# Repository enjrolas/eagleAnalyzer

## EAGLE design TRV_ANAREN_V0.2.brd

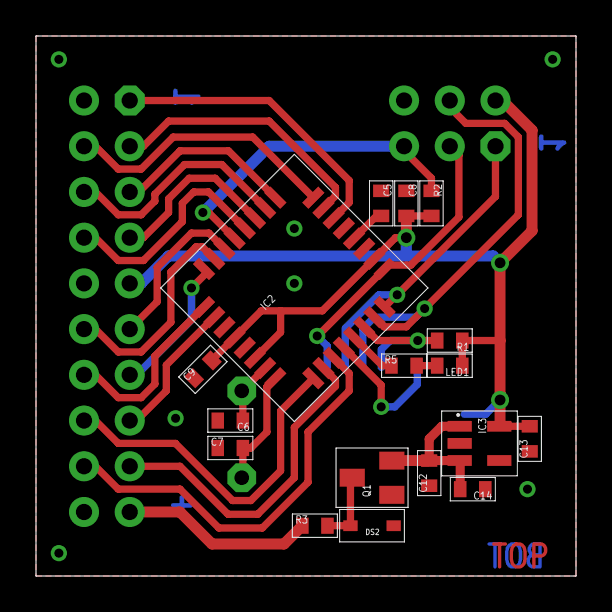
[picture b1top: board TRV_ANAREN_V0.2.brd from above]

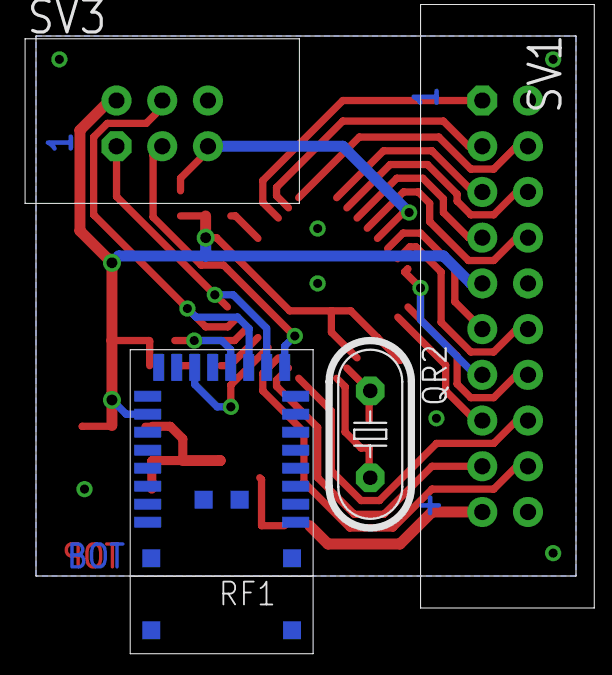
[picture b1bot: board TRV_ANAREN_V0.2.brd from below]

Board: 2 copper layers, 30.0 x 30.0 mm, 21 parts (4 on the bottom side), 31 nets.

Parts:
C5, C8, C9, C14: 100n; 0603
C6, C7: 22p; 0603
C12, C13: 1u; 0603
DS2: PESD12VL1BA; SOD323
IC2: MEGA168PA-AU; TQFP32-08
IC3: LP2992-IM5-3.3; SOT23-5
LED1: LEDR; 0603
Q1: IRLM9301; SOT23
QR2: 16.000; HC49U-V
R1, R2: 10k; 0603
R3: 0R; 0603
R5: 330R; 0603
RF1: ANAREN
SV1: ISP; ML20
SV3: ISP; ML6

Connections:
+3V3: C8.2, C9.2, C13.2, IC2.4, IC2.6, IC2.18, IC3.5, LED1.1, R1.1, R2.2, RF1.18, SV1.9, SV3.2
GND: C5.1, C6.2, C7.1, C8.1, C9.1, C12.1, C13.1, C14.1, DS2.C, IC2.3, IC2.5, IC2.21, IC3.2, Q1.1, RF1.8, RF1.17, SV1.10, SV1.20, SV3.6
LED: IC2.13, R5.1
MISO: IC2.16, RF1.10, SV3.1
MOSI: IC2.15, RF1.11, SV3.4
unnamed: IC2.22, SV1.1
unnamed: DS2.A, Q1.3, R3.2
unnamed: C5.2, IC2.20
unnamed: C12.2, C14.2, IC3.1, IC3.3, Q1.2
unnamed: C6.1, IC2.7, QR2.1
unnamed: C7.2, IC2.8, QR2.2
unnamed: LED1.2, R5.2
unnamed: R3.1, SV1.19
PC0: IC2.23, SV1.3
PC1: IC2.24, SV1.4
PC2: IC2.25, SV1.5
PC3: IC2.26, SV1.6
PC4: IC2.27, SV1.7
PC5: IC2.28, SV1.8
PD2: IC2.32, SV1.13
PD3: IC2.1, SV1.14
PD4: IC2.2, SV1.15
PD5: IC2.9, SV1.16
PD6: IC2.10, SV1.17
PD7: IC2.11, SV1.18
RIRQ: IC2.12, RF1.14
RSEL: IC2.14, R1.2, RF1.12
RST: IC2.29, R2.1, SV3.5
RXD: IC2.30, SV1.11
SCK: IC2.17, RF1.9, SV3.3
TXD: IC2.31, SV1.12

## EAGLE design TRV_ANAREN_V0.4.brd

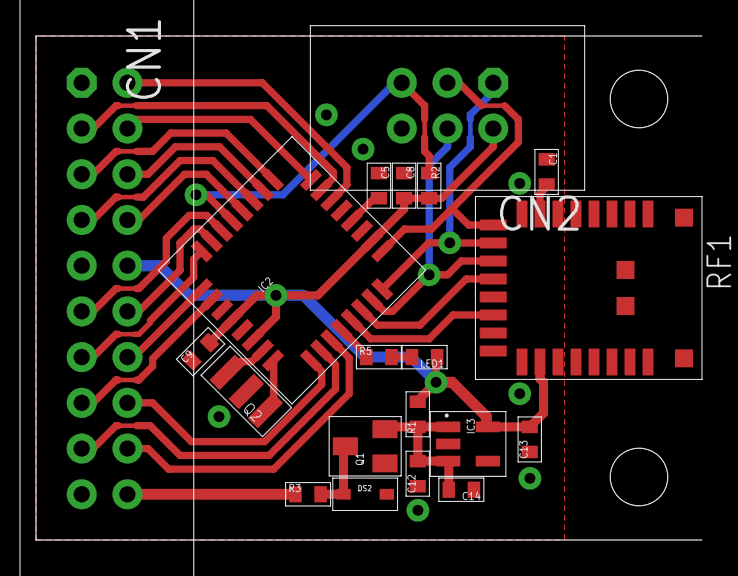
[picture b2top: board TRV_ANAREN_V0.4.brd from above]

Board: 2 copper layers, 37.0 x 28.0 mm, 20 parts (0 on the bottom side), 32 nets.

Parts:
C1: n.b.; 0603
C5, C8, C9, C14: 100n; 0603
C12, C13: 1u; 0603
CN1: EXT; ML20
CN2: ISP; ML6
DS2: PESD12VL1BA; SOD323
IC2: MEGA168PA-AU; TQFP32-08
IC3: LP2992-IM5-3.3; SOT23-5
LED1: LEDR; 0603
Q1: IRLM9301; SOT23
Q2: CR
R1: n.b.; 0603
R2: 10k; 0603
R3: 0R; 0603
R5: 330R; 0603
RF1: ANAREN_C

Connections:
+3V3: C8.2, C9.2, C13.2, CN1.10, CN2.2, IC2.4, IC2.6, IC2.18, IC3.5, LED1.1, R1.2, R2.2, RF1.18
GND: C1.1, C5.1, C8.1, C9.1, C12.1, C13.1, C14.1, CN1.9, CN1.19, CN2.6, DS2.A, IC2.3, IC2.5, IC2.21, IC3.2, Q1.1, Q2.M, RF1.8, RF1.17
MISO: CN2.1, IC2.16, RF1.10
MOSI: CN2.4, IC2.15, RF1.11
unnamed: C1.2, RF1.7
unnamed: IC2.12, R5.1
unnamed: CN1.2, IC2.22
unnamed: DS2.C, Q1.3, R3.2
unnamed: C5.2, IC2.20
unnamed: C12.2, C14.2, IC3.1, IC3.3, Q1.2, R1.1
unnamed: IC2.7, Q2.2
unnamed: IC2.8, Q2.1
unnamed: LED1.2, R5.2
PC0: CN1.3, IC2.23
PC1: CN1.4, IC2.24
PC2: CN1.5, IC2.25
PC3: CN1.6, IC2.26
PC4: CN1.7, IC2.27
PC5: CN1.8, IC2.28
PD2: CN1.13, IC2.32
PD3: CN1.14, IC2.1
PD4: CN1.15, IC2.2
PD5: CN1.16, IC2.9
PD6: CN1.17, IC2.10
PD7: CN1.18, IC2.11
RIRQ: IC2.13, RF1.14
RSEL: IC2.14, RF1.12
RST: CN2.5, IC2.29, R2.1
RXD: CN1.11, IC2.30
SCK: CN2.3, IC2.17, RF1.9
TXD: CN1.12, IC2.31
VIN: CN1.20, R3.1

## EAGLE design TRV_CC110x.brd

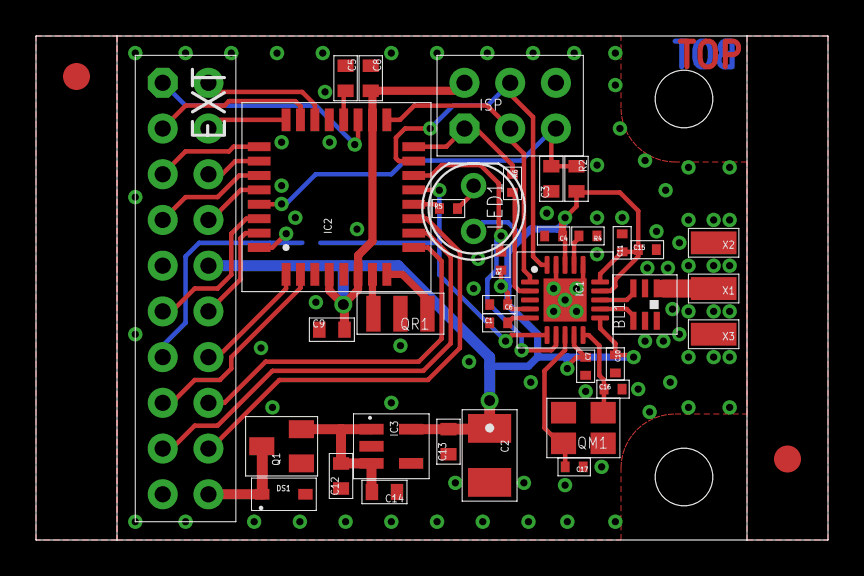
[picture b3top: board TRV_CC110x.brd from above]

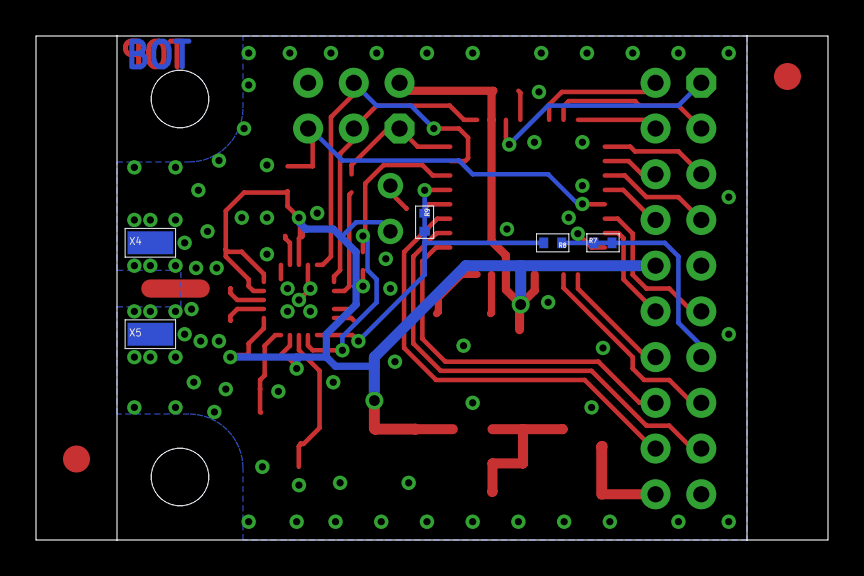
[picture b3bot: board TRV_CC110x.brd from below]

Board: 2 copper layers, 44.0 x 28.0 mm, 43 parts (5 on the bottom side), 39 nets.

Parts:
BL1: 089BM15A0001; BL
C1, C6: 100n; 0402
C2: 10u; SMC_B
C3, C5, C8, C9, C14: 100n; 0603
C4, C11: 220p; 0402
C7, C15: 10n; 0402
C10: 2p2; 0402
C12, C13: 1u; 0603
C16, C17: 27p; 0402
DS1: PESD12VL1BA; SOD323
EXT: EXT; ML20S
IC1: VQFN20
IC2: MEGA328P-AU; TQFP32-08
IC3: LP2992-IM5-3.3; SOT23-5
ISP: ISP; ML6S
LED1: LEDR; T1-3/4
Q1: IRLML9301; SOT23
QM1: 26M; SMD_4P_3.2X2.5
QR1: 8M; CR
R1: 10k; 0402
R2: 10k; 0603
R4: 56k; 0402
R5, R6: 330R; 0402
R7, R8, R9: 0402
U$3, U$4: FUICIDAL1.5R
X1: ANT; S2.54/1.27
X2, X3, X4, X5: GND; S2.54/1.27

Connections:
+3V3: C2.+, C4.1, C6.1, C7.1, C8.2, C9.2, C10.1, C11.1, C13.2, C15.1, EXT.10, IC1.-4, IC1.-9, IC1.-11, IC1.-14, IC1.-15, IC1.-18, IC2.4, IC2.6, IC2.18, IC3.5, ISP.2, LED1.A, R1.1, R2.2
GND: BL1.2, BL1.5, BL1.6, C1.1, C2.-, C3.1, C4.2, C5.1, C6.2, C7.2, C8.1, C9.1, C10.2, C11.2, C12.1, C13.1, C14.1, C15.2, C16.2, C17.1, DS1.A, EXT.9, EXT.19, IC1.-16, IC1.-19, IC1.P, IC2.3, IC2.5, IC2.21, IC3.2, ISP.6, Q1.1, QM1.2, QM1.4, QR1.M, R4.1, X2.1, X3.1, X4.1, X5.1
MISO: IC2.16, ISP.1, R6.1
MOSI: IC1.-20, IC2.15, ISP.4
unnamed: C1.2, IC1.-5
unnamed: IC1.-17, R4.2
unnamed: EXT.2, IC2.22
unnamed: IC1.-2, R6.2
unnamed: DS1.C, EXT.20, Q1.3
unnamed: C5.2, IC2.20
unnamed: IC2.8, QR1.1
unnamed: IC2.7, QR1.2
unnamed: IC2.12, R5.1
unnamed: EXT.13, IC2.32, R7.1, R7.2, R8.1
unnamed: C12.2, C14.2, IC3.1, IC3.3, Q1.2
unnamed: BL1.3, IC1.-13
unnamed: BL1.4, IC1.-12
unnamed: EXT.1, IC2.19
unnamed: BL1.1, X1.1
unnamed: C17.2, IC1.-8, QM1.3
unnamed: C16.1, IC1.-10, QM1.1
unnamed: LED1.C, R5.2
PC0: EXT.3, IC2.23
PC1: EXT.4, IC2.24
PC2: EXT.5, IC2.25
PC3: EXT.6, IC2.26
PC4: EXT.7, IC2.27
PC5: EXT.8, IC2.28
PD3: EXT.14, IC2.1
PD4: EXT.15, IC2.2
PD5: EXT.16, IC2.9
PD6: EXT.17, IC2.10
PD7: EXT.18, IC2.11
RIRQ: IC1.-6, IC2.13, R8.2, R9.1, R9.2
RSEL: IC1.-7, IC2.14, R1.2
RST: C3.2, IC2.29, ISP.5, R2.1
RXD: EXT.11, IC2.30
SCK: IC1.-1, IC2.17, ISP.3
TXD: EXT.12, IC2.31
